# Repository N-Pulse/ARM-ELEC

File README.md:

# N-Pulse Prosthetic Safety System

> **EPFL N-Pulse — Spring Semester 2026**  
> Firmware and GUI for the safety monitoring board of the N-Pulse transradial bionic arm prosthesis.  
> For background on sensor selection rationale, thresholds, and design decisions, refer to the accompanying report.

---

## Repository Structure

```
/
├── GUI/
│   └── serial_dashboard.py        # Plotly Dash web dashboard — reads serial CSV and plots live telemetry
│
└── prosthetic_safety/
    ├── prosthetic_safety.ino      # Arduino sketch entry point (setup + loop)
    ├── Config.h                   # ⬅ All pin assignments, I2C addresses, thresholds — edit here first
    ├── DataTypes.h / .cpp         # Structs (TH_Reading, PowerReading, IMUReading, SafetyFlags) and global sensor objects
    ├── Setup.h / .cpp             # Sensor initialisation and interrupt attachment
    ├── Sensors.h / .cpp           # Sensor read functions (non-blocking DS18B20, SHT41, Si7021, INA260, LIS3DH)
    ├── Safety.h / .cpp            # Fault evaluation logic + ISR handlers
    ├── Logging.h / .cpp           # CSV serial output and SD card stub
    └── Utils.h / .cpp             # Helpers: ROM printing, threshold lookups, raw IMU register I/O
```

---

## Hardware Connections

The system uses two I2C buses on the Adafruit Metro ESP32-S3. Bus 0 (`Wire`, default pins) and Bus 1 (`Wire1`, pins 9 SDA / 10 SCL) are both active simultaneously.

### Pin Map (from `Config.h`)

| Signal | ESP32-S3 Pin | Connected to |
|--------|-------------|--------------|
| SDA0 | Pin SDA | DS2484 bus0, INA260, LIS3DH, SHT41 bus0 |
| SCL0 | Pin SCL | Same as above |
| SDA1 | Pin 9 | DS2484 bus1, SHT41 bus1, Si7021 |
| SCL1 | Pin 10 | Same as above |
| 1-Wire direct | Pin 7 | Battery, socket, and 1 motor DS18B20 (no bridge chip) |
| IMU interrupt | Pin 5 | LIS3DH INT1 → MCU (active-low, pull-up enabled) |
| Current alert | Pin 6 | INA260 ALERT → MCU (active-low, pull-up enabled, latching) |
| Power cut | Pin 11 | Pololu switch CTRL — pull **LOW** to cut load power |

### Wiring Diagram

#### JST cable labels

#### Current interupt test-bench wiring

Depending on the setup, it may be beneficial to make sure VIN- is the same as the systems GND (e.g. when using a lab alim), then wire like on the image (with the jumper). When trying to use the sensor on the test bench with the battery for example, simple pass the high or low cable of the battery through the VIN+ to VIN-. You might want remove the jumper and potentiometer to avoid any confusion in the wiring (unless the grounding is still useful). 

#### Full test-bench

Refer to this image to wire the test bench correctly.

Also note there are 3D printed motor mounts (orange), which can be used to test the motor under load and the thermal sensors. 

#### System-level block diagram and hand-level schematic: 

### I2C Address Map

| Device | Bus | Address | Notes |
|--------|-----|---------|-------|
| DS2484 (×2) | 0 and 1 | `0x18` | Fixed — one per bus to avoid collision |
| LIS3DH | 0 | `0x19` | SDO tied HIGH |
| INA260 | 0 | `0x40` | A0/A1 default |
| SHT41 (×2) | 0 and 1 | `0x44` | Fixed — one per bus to avoid collision |
| Si7021 | 1 | `0x40` | Shares bus 1 with SHT41, different from INA260 on bus 0 |

### DS18B20 Temperature Sensor Topology

Nine DS18B20s are distributed across three 1-Wire lines:

- **Bus 0 (via DS2484 on I2C bus 0):** 3 motor sensors in the hand
- **Bus 1 (via DS2484 on I2C bus 1):** 3 motor sensors in the hand
- **Direct line (pin 7, no bridge):** battery sensor, socket/stump contact sensor, 1 motor sensor

Each DS18B20 line needs a **4.7 kΩ pull-up resistor between DQ and 3.3 V** (but the ones passed in I2C already have a sufficient pullup resistance through the DS2484). The direct line uses the `DallasTemperature` library at **9-bit resolution** (94 ms conversion time, 0.5 °C) for faster updates. The DS2484-bridged lines use the `Adafruit_DS248x` library and the same 94 ms window.

### Power Cut Circuit

```
Battery (+) ──► Power Switch VIN ──► Prosthetic rail (+)
Battery (−) ──► Power Switch GND            ──► Prosthetic rail (−)
                        │
               ESP32-S3 Pin 11 ──► CTRL (LOW = power cut)
```

`PIN_POWER_CUT` is driven LOW by either the main loop (`requestPowerCut()`) or directly from the ISR for minimum latency on overcurrent and shock events.

---

## Sensor Discovery & Address Registration

**When new DS18B20 sensors are installed, their ROM addresses must be registered in `Config.h`.** (This should be already correct if the test-bench wasn't changed.) The firmware will print every discovered ROM to the serial monitor at startup — run the sketch once, note the ROM codes, then fill in the `bus0_sensors[]`, `bus1_sensors[]`, and `direct_sensors[]` arrays with the appropriate `SensorPurpose` and per-sensor temperature limit.

```cpp
// Example entry in Config.h
static constexpr SensorMapping direct_sensors[] = {
  {{ 0x28, 0xFF, 0x64, 0x0E, 0x6D, 0x54, 0x36, 0xC9 }, SensorPurpose::BATTERY, 45.0f },
  {{ 0x28, 0xFF, 0x64, 0x0E, 0x6D, 0x86, 0x2C, 0xE3 }, SensorPurpose::SOCKET,  41.0f },
  ...
};
```

Per-sensor limits (battery: 45 °C, socket contact: 41 °C, motors: 85 °C) are looked up at runtime by ROM address in `getSensorTempLimit()` (`Utils.cpp`). If a sensor's ROM is not in the table, it falls back to `MAX_TEMP_C`.

---

## INA260 Current Sensor — Bench Test

The INA260 sits in **series** with the battery. Before installing in the arm, validate it on a bench:

### Wiring for the test

```
Bench PSU (+) ──► INA260 IN+ ──► INA260 IN− ──► Load ──► Bench PSU (−)
                     │
              I2C to ESP32-S3 (bus 0, address 0x40)
              ALERT pin → ESP32-S3 pin 6
```

> ⚠️ The INA260 has **no galvanic isolation** between the battery ground and the board ground. Make sure both share the same ground reference, or use an isolated bench PSU. (That is the case on the test-bench)

### Recommended bench settings

| Parameter | Value |
|-----------|-------|
| PSU voltage | **12 V** |
| PSU current limit | **100 mA** |

The alert pin is configured in hardware for **overcurrent** (fires when current exceeds `Config::MAX_CURRENT_MA`). During bench testing, `MAX_CURRENT_MA` is set to 40 mA so the alert fires well within the PSU limit — set it back to 5300 mA (or appropriate value) for normal prosthetic operation.

---

## Arduino Libraries Required

Install all of the following via the Arduino Library Manager before compiling:

| Library | Used for |
|---------|---------|
| `Adafruit_INA260` | Current/voltage sensor |
| `Adafruit_LIS3DH` + `Adafruit_Sensor` | IMU |
| `Adafruit_Si7021` | Humidity/temp sensor (socket) |
| `7semi_SHT4x` | Humidity/temp sensors (hand/wrist) |
| `Adafruit_DS248x` | I2C-to-1-Wire bridge (DS2484) |
| `DallasTemperature` | Direct 1-Wire DS18B20 (no bridge) |
| `OneWire` | Required by DallasTemperature |

**Board:** Adafruit Metro ESP32-S3 (install via Arduino Boards Manager → search "esp32" by Espressif).

---

## Uploading the Firmware

1. Open `prosthetic_safety/prosthetic_safety.ino` in Arduino IDE.
2. Select **Board → Adafruit Metro ESP32-S3** and the correct COM/tty port.
3. Upload. On first boot, watch the serial monitor at **115 200 baud** — setup messages are prefixed with `[SETUP]`. Any sensor not found will print a warning; the ROM addresses of all discovered DS18B20s are printed here for registration.

---

## GUI — Live Telemetry Dashboard

`GUI/serial_dashboard.py` is a Plotly Dash web app. It reads the CSV stream from the serial port and displays five real-time subplots plus status LEDs for each safety flag.

### Install dependencies

```bash
pip install pyserial dash plotly pandas
```

### Configure the port

Edit the top of `serial_dashboard.py`:

```python
SERIAL_PORT   = '/dev/cu.usbmodem101'   
BAUD_RATE     = 115200
```
Replace with the correct port address. 

### Run

```bash
python GUI/serial_dashboard.py
```

Then open **http://127.0.0.1:8050** in any browser. The dashboard auto-reconnects if the serial connection drops.

### What is displayed

| Panel | Channels |
|-------|---------|
| Motor Temperatures | bus0_ds1–3, bus1_ds1–3, direct_ds1, socket contact, battery |
| Body Temperatures | Hand, wrist, socket ambient (SHT41 + Si7021) |
| Relative Humidity | Hand, wrist, socket (SHT41 + Si7021) |
| IMU Data | ax, ay, az [g] + vector magnitude |
| Power Data | Current [mA], voltage [V], power [mW] |
| Status LEDs | Temp limit, humidity limit, overcurrent, shock, power cut, sensors OK |

At startup the dashboard performs a one-time health check: any channel that reads `nan`, 0.0 (humidity), or below −10 °C (temperature) is automatically deselected. You can re-enable channels manually using the checklist below the plots.

### CSV format

The firmware emits one comma-separated line every 500 ms (configurable via `Config::LOG_PERIOD_MS`). Lines starting with `#` are ignored by the dashboard. The exact column order is:

```
t_ms, hand_temp_c, hand_rh, wrist_temp_c, wrist_rh, socket_temp_c, socket_rh,
bus0_ds1_c, bus0_ds2_c, bus0_ds3_c, bus1_ds1_c, bus1_ds2_c, bus1_ds3_c,
battery, socket, direct_ds1_c,
imu_ax_g, imu_ay_g, imu_az_g, imu_mag_g,
current_ma, bus_mv, power_mw,
temp_limit_flag, humidity_limit_flag, overcurrent_limit_flag,
shock_flag, power_cut_flag, sensors_ok
```

The code defaults with `PRINT_CSV_HEADER_AT_BOOT = false`. To have the CSV header printed at startup for easier CSV reading, simply set that to `true`.

---

## Enabling Power Cut Actions

All four power-cut triggers are **disabled by default** in `Config.h` for safe development:

```cpp
static const bool ENABLE_POWER_CUT_ON_OVERCURRENT        = false;
static const bool ENABLE_POWER_CUT_ON_OVERHEAT           = false;
static const bool ENABLE_POWER_CUT_ON_OVERHUMIDITY       = false;
static const bool ENABLE_POWER_CUT_ON_CONFIRMED_SHOCK    = false;
```

Set the relevant flag(s) to `true` once you have validated each sensor path end-to-end. The overcurrent and shock paths trigger from the ISR (minimum latency); overheat and humidity are evaluated in the main loop every `LOG_PERIOD_MS`.

Once a power cut is triggered, it **latches** — the flag does not reset automatically. A manual reset (power cycle or serial command) is required before the safety system will re-arm.

## Troubleshooting

If one of the lines is not being detected, it often happens that the pins are not well plugged in on the MCU (the pins tend to slip out).

## What to Add Next

- **SD card logging** — `logToSDCard()` in `Logging.cpp` is empty. The Metro ESP32-S3 has a built-in MicroSD slot and it would be a useful feature for the safety system. 
- **Using MCU Wireless capabilities** — The ESP32-S3 supports WiFi and Bluetooth; useful for reading data without cable connection with the arm.
- **CAN / UART protocol** — Define how fault codes are forwarded to the main prosthetic control board.
- **Prediction capabilities** - The MCU was chosen with a little extra horse power to be able to handle more demanding computations. One idea was to compute gradients and estiimate if one of the metrics was going to exceed the threshold and add a warning. 

## Other

There are two Adafruit DS2484 1Wire to I2C breakout boards left in the box with the test bench.

## Contributors

| Name | Role | Semester |
|------|------|----------|
| Mathis Finckh | Safety System Design & Implementation | Spring 2026 |

*Please update this table when you pick up the project.*

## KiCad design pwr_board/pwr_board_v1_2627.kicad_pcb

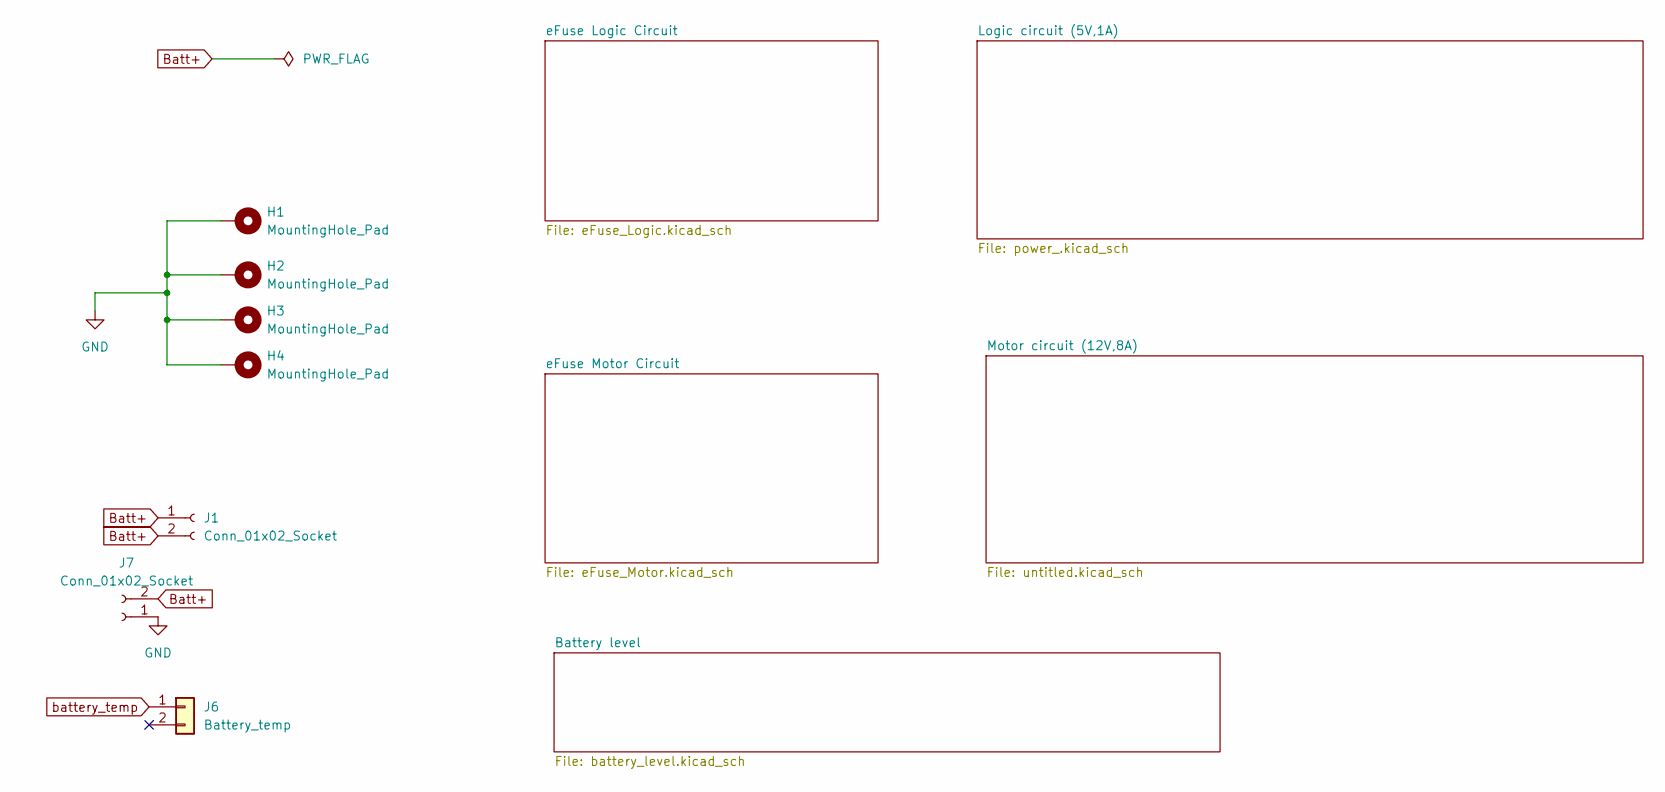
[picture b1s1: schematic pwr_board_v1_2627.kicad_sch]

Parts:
H1, H2, H3, H4: MountingHole_Pad; MountingHole_2.1mm
J1: Conn_01x02_Socket; SolderWire-0.75sqmm_1x02_P4.8mm_D1.25mm_OD2.3mm
J6: Battery_temp; Conn_12V_2A5040500291
J7: Conn_01x02_Socket; AMASS_XT30PW-F_1x02_P2.50mm_Horizontal

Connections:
Batt+: J1.1, J1.2, J7.2; also elsewhere on the board
GND: H1.1, H2.1, H3.1, H4.1, J7.1; also elsewhere on the board
battery_temp: J6.1 (Pin_1_1); also elsewhere on the board

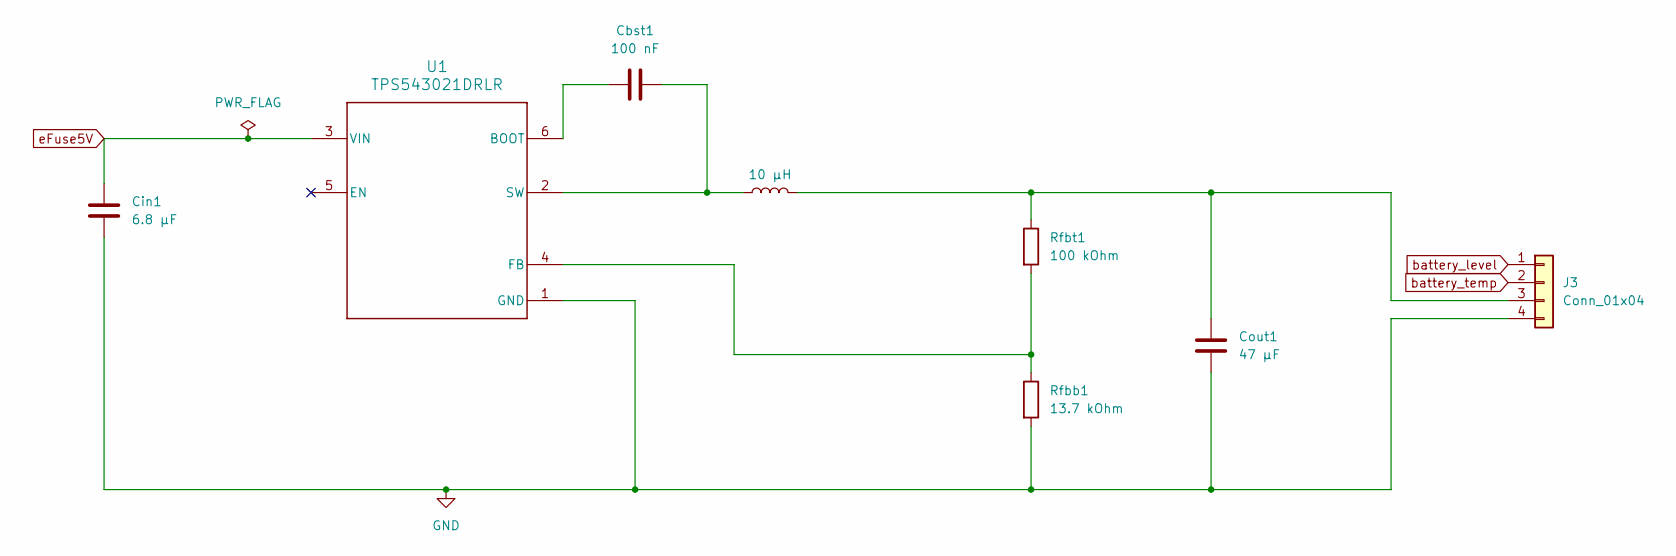
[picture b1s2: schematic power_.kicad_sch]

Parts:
Cbst1: 100 nF; C_0603_1608Metric
Cin1: 6.8 µF; C_0603_1608Metric
Cout1: 47 µF; C_0603_1608Metric
J3: Conn_01x04; 01x04_PicoLocck_Con_5037630491
L2: 10 µH; L2_74438324100
Rfbb1: 13.7 kOhm; R_0402_1005Metric
Rfbt1: 100 kOhm; R_0402_1005Metric
U1: TPS543021DRLR; Buck-5V-1A-TPS543021DRL

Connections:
GND: Cin1.2, Cout1.2, J3.4, Rfbb1.2, U1.1 (GND); also elsewhere on the board
unnamed: Cout1.1, J3.3, L2.2, Rfbt1.1
unnamed: Cbst1.1, U1.6 (BOOT)
unnamed: Rfbb1.1, Rfbt1.2, U1.4 (FB)
unnamed: Cbst1.2, L2.1, U1.2 (SW)
battery_level: J3.1; also elsewhere on the board
battery_temp: J3.2; also elsewhere on the board
eFuse5V: Cin1.1, U1.3 (VIN); also elsewhere on the board

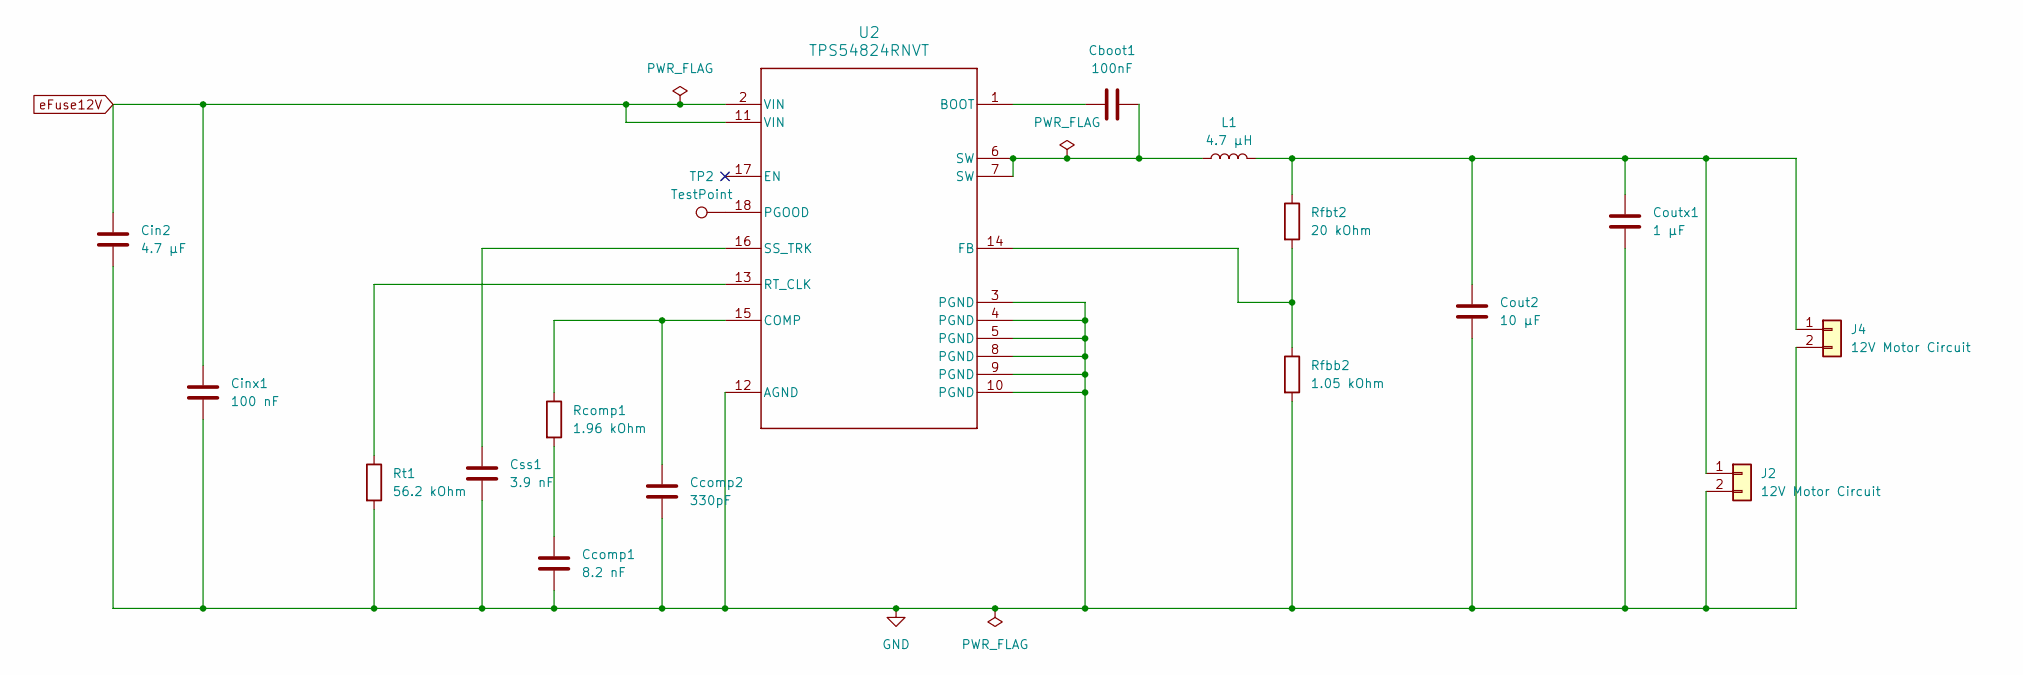
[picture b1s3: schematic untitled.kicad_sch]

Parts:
Cboot1: 100nF; C_0603_1608Metric
Ccomp1: 8.2 nF; C_0603_1608Metric
Ccomp2: 330pF; C_0603_1608Metric
Cin2: 4.7 µF; C_0603_1608Metric
Cinx1: 100 nF; C_0603_1608Metric
Cout2: 10 µF; C_0603_1608Metric
Coutx1: 1 µF; C_0603_1608Metric
Css1: 3.9 nF; C_0603_1608Metric
J2: 12V Motor Circuit; Conn_12V_2A5040500291
J4: 12V Motor Circuit; conn_12_6A__2053380000-SD_02_MOL
L1: 4.7 µH; L1_SRP5030HMCT100M
Rcomp1: 1.96 kOhm; R_0402_1005Metric
Rfbb2: 1.05 kOhm; R_0402_1005Metric
Rfbt2: 20 kOhm; R_0402_1005Metric
Rt1: 56.2 kOhm; R_0402_1005Metric
TP2: TestPoint; TestPoint_THTPad_1.5x1.5mm_Drill0.7mm
U2: TPS54824RNVT; MotorCircuit-Buck-12V-8A-TPS54824RNVT

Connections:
GND: Ccomp1.2, Ccomp2.2, Cin2.2, Cinx1.2, Cout2.2, Coutx1.2, Css1.2, J2.2, J4.2, Rfbb2.2, Rt1.2, U2.3 (PGND), U2.4 (PGND), U2.5 (PGND), U2.8 (PGND), U2.9 (PGND), U2.10 (PGND), U2.12 (AGND); also elsewhere on the board
unnamed: Cboot1.2, L1.1, U2.6 (SW), U2.7 (SW)
unnamed: Ccomp1.1, Rcomp1.2
unnamed: Cout2.1, Coutx1.1, J2.1, J4.1, L1.2, Rfbt2.1
unnamed: Cboot1.1, U2.1 (BOOT)
unnamed: Ccomp2.1, Rcomp1.1, U2.15 (COMP)
unnamed: Rfbb2.1, Rfbt2.2, U2.14 (FB)
unnamed: TP2.1 (1_1), U2.18 (PGOOD)
unnamed: Rt1.1, U2.13 (RT_CLK)
unnamed: Css1.1, U2.16 (SS_TRK)
eFuse12V: Cin2.1, Cinx1.1, U2.2 (VIN), U2.11 (VIN); also elsewhere on the board

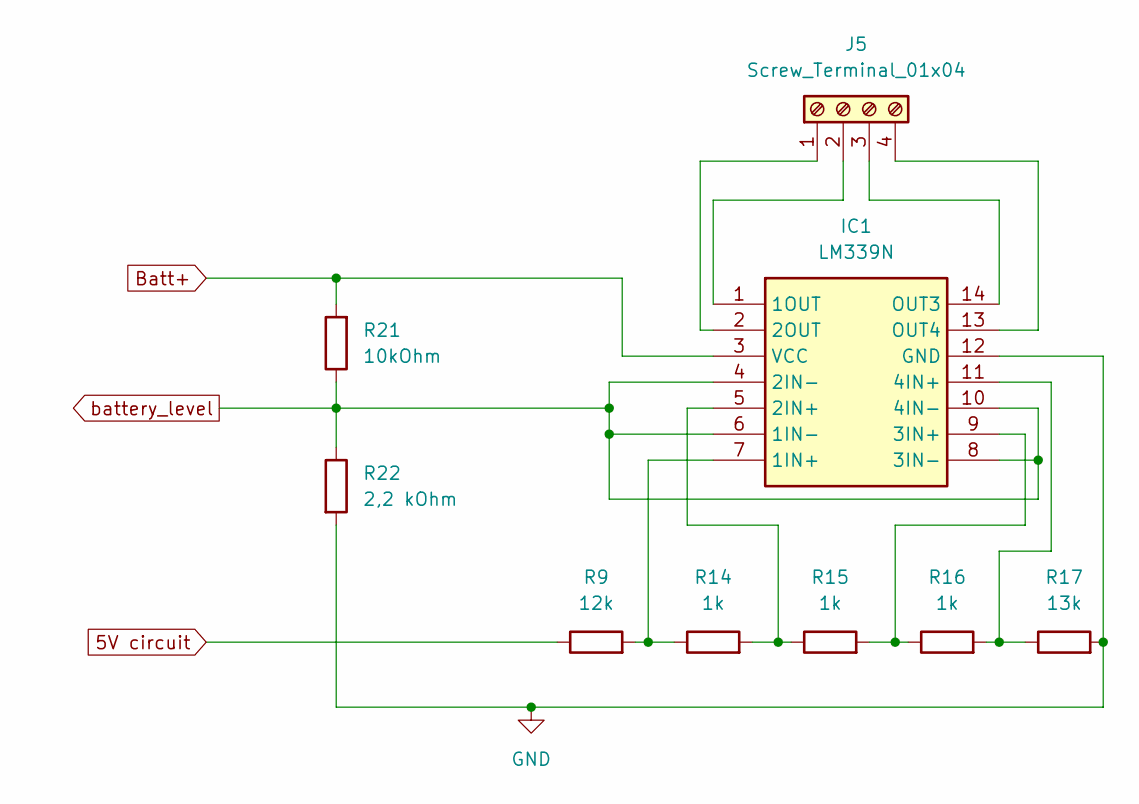
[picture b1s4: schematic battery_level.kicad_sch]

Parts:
IC1: LM339N; SOP65P640X120-14N_batt_lvl; Mouser Part Number 595-LM339N
J5: Screw_Terminal_01x04; 01x04_PicoLocck_Con_5037630491
R9: 12k; R_0402_1005Metric
R14, R15, R16: 1k; R_0402_1005Metric
R17: 13k; R_0402_1005Metric
R21: 10kOhm; R_0402_1005Metric
R22: 2,2 kOhm; R_0402_1005Metric

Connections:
5V circuit: R9.1
Batt+: IC1.3 (VCC), R21.2; also elsewhere on the board
GND: IC1.12 (GND), R17.2, R22.2; also elsewhere on the board
unnamed: IC1.7 (1IN+), R9.2, R14.1
unnamed: IC1.1 (1OUT), J5.2
unnamed: IC1.5 (2IN+), R14.2, R15.1
unnamed: IC1.2 (2OUT), J5.1
unnamed: IC1.9 (3IN+), R15.2, R16.1
unnamed: IC1.11 (4IN+), R16.2, R17.1
unnamed: IC1.14 (OUT3), J5.3
unnamed: IC1.13 (OUT4), J5.4
battery_level: IC1.4 (2IN-), IC1.6 (1IN-), IC1.8 (3IN-), IC1.10 (4IN-), R21.1, R22.1; also elsewhere on the board

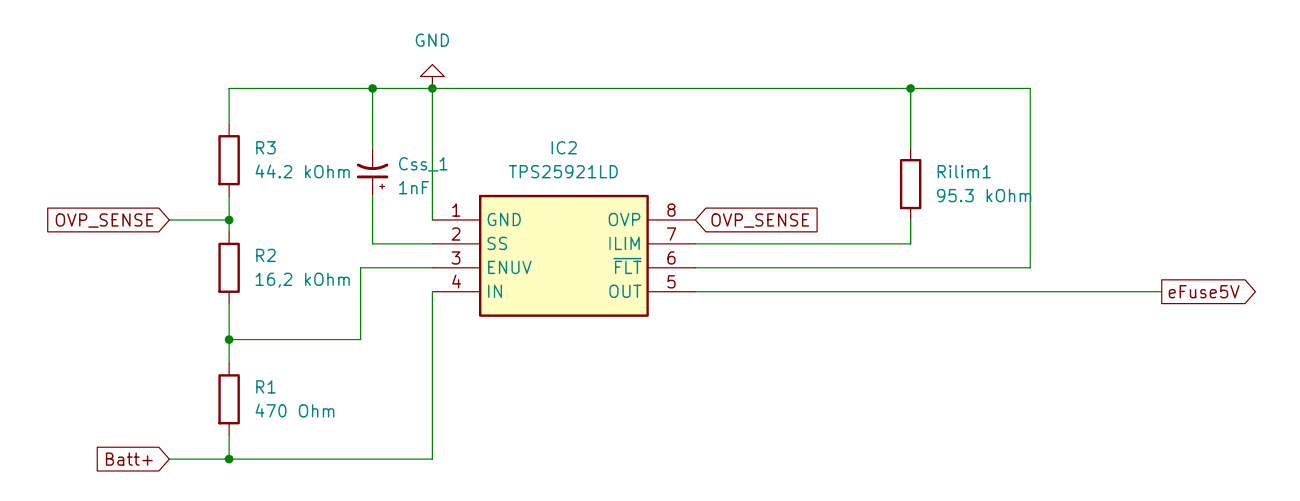
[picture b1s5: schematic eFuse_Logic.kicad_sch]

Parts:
Css_1: 1nF; C_0603_1608Metric
IC2: TPS25921LD; eFuse_Logic; Mouser Part Number 595-TPS25921LD
R1: 470 Ohm; R_0402_1005Metric
R2: 16,2 kOhm; R_0402_1005Metric
R3: 44.2 kOhm; R_0402_1005Metric
Rilim1: 95.3 kOhm; R_0402_1005Metric

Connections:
Batt+: IC2.4 (IN), R1.2; also elsewhere on the board
GND: Css_1.2, IC2.1 (GND), IC2.6 (~FLT), R3.1, Rilim1.1; also elsewhere on the board
unnamed: IC2.3 (ENUV), R1.1, R2.2
unnamed: IC2.7 (ILIM), Rilim1.2
unnamed: Css_1.1, IC2.2 (SS)
OVP_SENSE: IC2.8 (OVP), R2.1, R3.2
eFuse5V: IC2.5 (OUT); also elsewhere on the board

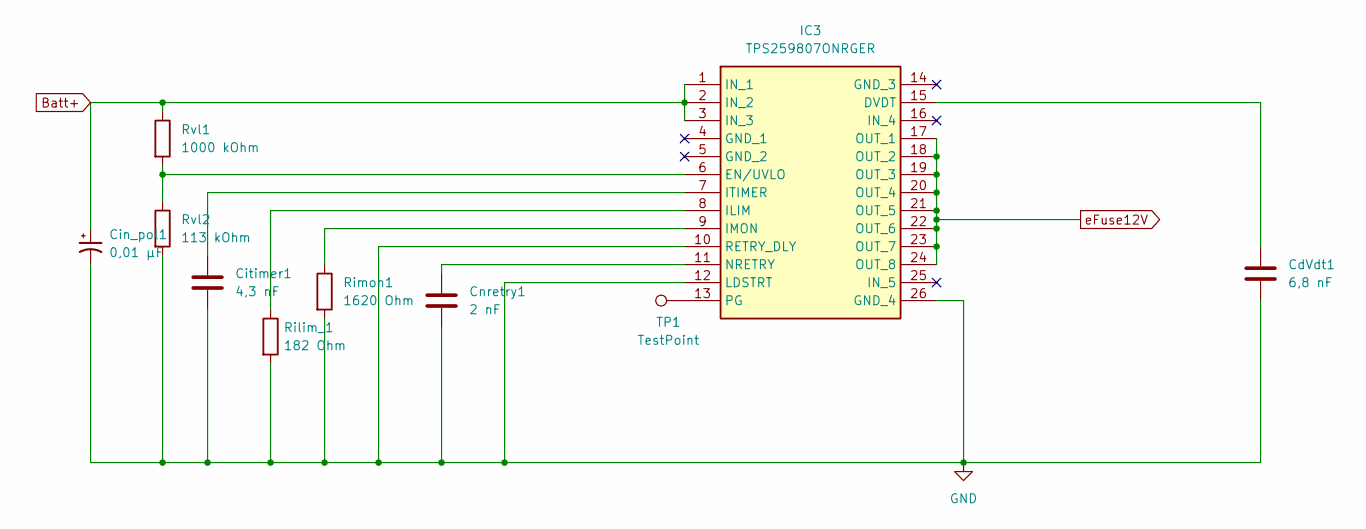
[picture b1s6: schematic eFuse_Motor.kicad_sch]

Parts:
CdVdt1: 6,8 nF; C_0603_1608Metric
Cin_pol1: 0,01 µF; C_0603_1608Metric
Citimer1: 4,3 nF; C_0603_1608Metric
Cnretry1: 2 nF; C_0603_1608Metric
IC3: TPS259807ONRGER; eFuse_Motor; Mouser Part Number 595-TPS259807ONRGER
Rilim_1: 182 Ohm; R_0402_1005Metric
Rimon1: 1620 Ohm; R_0402_1005Metric
Rvl1: 1000 kOhm; R_0402_1005Metric
Rvl2: 113 kOhm; R_0402_1005Metric
TP1: TestPoint; TestPoint_THTPad_1.5x1.5mm_Drill0.7mm

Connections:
Batt+: Cin_pol1.1, IC3.1 (IN_1), IC3.2 (IN_2), IC3.3 (IN_3), Rvl1.1; also elsewhere on the board
GND: CdVdt1.2, Cin_pol1.2, Citimer1.2, Cnretry1.2, IC3.10 (RETRY_DLY), IC3.12 (LDSTRT), IC3.26 (GND_4), Rilim_1.2, Rimon1.2, Rvl2.2; also elsewhere on the board
unnamed: CdVdt1.1, IC3.15 (DVDT)
unnamed: IC3.6 (EN/UVLO), Rvl1.2, Rvl2.1
unnamed: IC3.8 (ILIM), Rilim_1.1
unnamed: IC3.9 (IMON), Rimon1.1
unnamed: Citimer1.1, IC3.7 (ITIMER)
unnamed: Cnretry1.1, IC3.11 (NRETRY)
unnamed: IC3.13 (PG), TP1.1 (1_1)
eFuse12V: IC3.17 (OUT_1), IC3.18 (OUT_2), IC3.19 (OUT_3), IC3.20 (OUT_4), IC3.21 (OUT_5), IC3.22 (OUT_6), IC3.23 (OUT_7), IC3.24 (OUT_8); also elsewhere on the board

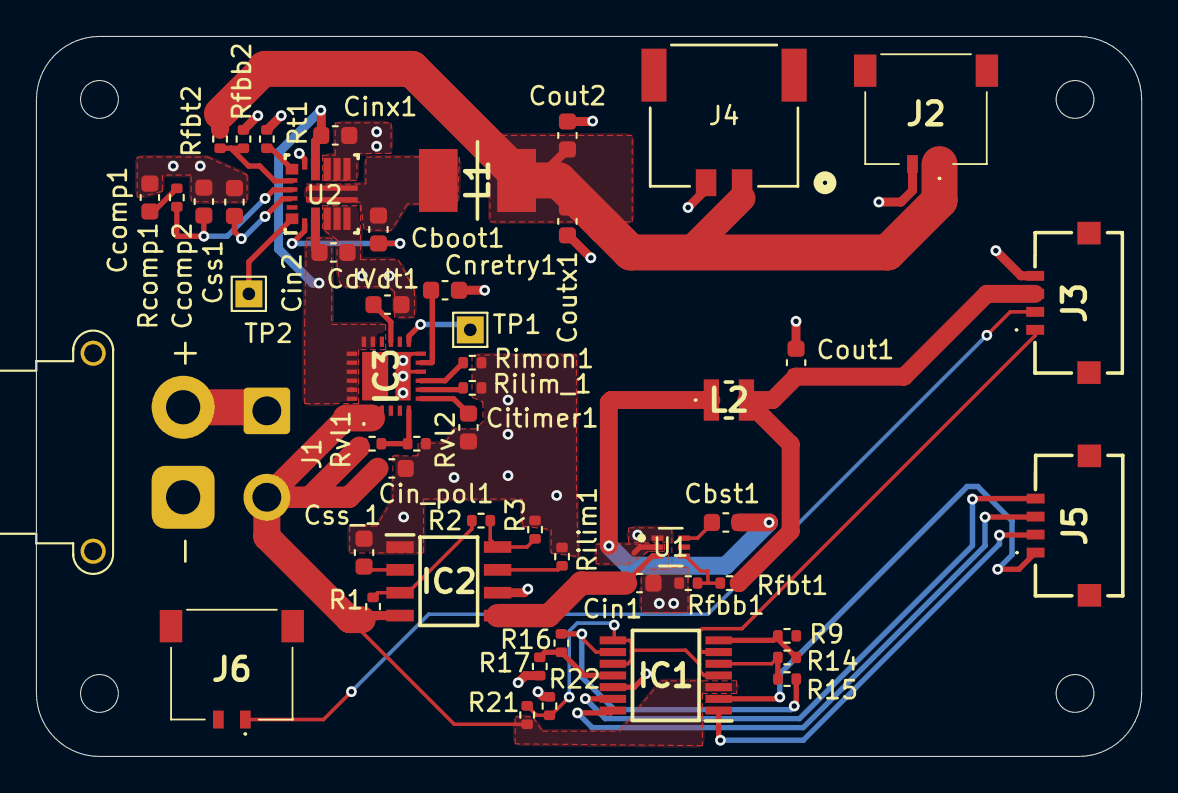
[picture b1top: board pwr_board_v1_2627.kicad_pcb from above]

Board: 2 copper layers, 61.4 x 40.0 mm, 57 parts (0 on the bottom side), 38 nets.

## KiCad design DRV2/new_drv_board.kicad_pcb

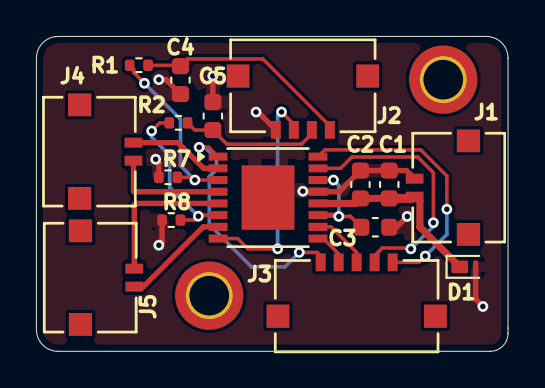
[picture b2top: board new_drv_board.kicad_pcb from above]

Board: 2 copper layers, 26.2 x 17.5 mm, 18 parts (0 on the bottom side), 17 nets.

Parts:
C1: 0.1µF; C_0603_1608Metric
C2: 10µF; C_0603_1608Metric
C3: 2.2µF; C_0603_1608Metric
C4, C5: 100nF; C_0603_1608Metric
D1: PTVS12VZ1USK; Nexperia_DSN1608-2_1.6x0.8mm
H1, H2: MountingHole; MountingHole_2.2mm_M2_DIN965_Pad_TopBottom
J1, J5: Conn_01x02; CONN_5037630000-SD_02_MOL
J2: Conn_01x04; CONN_5037630000-SD_04_MOL
J3: Conn_01x05; CONN_5037630000-SD_05_MOL
J4: CONN_5037630000-SD_02_MOL
R1, R2: 100Ω; R_0402_1005Metric
R7, R8: 500mΩ; R_0402_1005Metric
U1: DRV8848; TSSOP-16-1EP_4.4x5mm_P0.65mm

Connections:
+12V: C1.1, C2.1, D1.1 (K), J1.1, U1.12 (VM)
/Curr7: R1.1, R7.1, U1.3 (AISEN)
/Curr8: R2.1, R8.1, U1.6 (BISEN)
/IN7-1: J3.5, U1.16 (AIN1)
/IN7-2: J3.4, U1.15 (AIN2)
/IN8-1: J3.2, U1.9 (BIN1)
/IN8-2: J3.3, U1.10 (BIN2)
/OUT7-1: J4.1, U1.2 (AOUT1)
/OUT7-2: J4.2, U1.4 (AOUT2)
/OUT8-1: J5.2, U1.7 (BOUT1)
/OUT8-2: J5.1, U1.5 (BOUT2)
/nFAULT: J2.3, U1.8 (~FAULT)
/sleep: J3.1, U1.1 (~SLEEP)
GND: C1.2, C2.2, C3.2, C4.1, C5.2, D1.2 (A), J1.2, J2.4, R7.2, R8.2, U1.13 (GND), U1.17 (GND)
unnamed: C4.2, J2.1, R1.2
unnamed: C5.1, J2.2, R2.2
unnamed: C3.1, U1.11 (VREF), U1.14 (VINT)

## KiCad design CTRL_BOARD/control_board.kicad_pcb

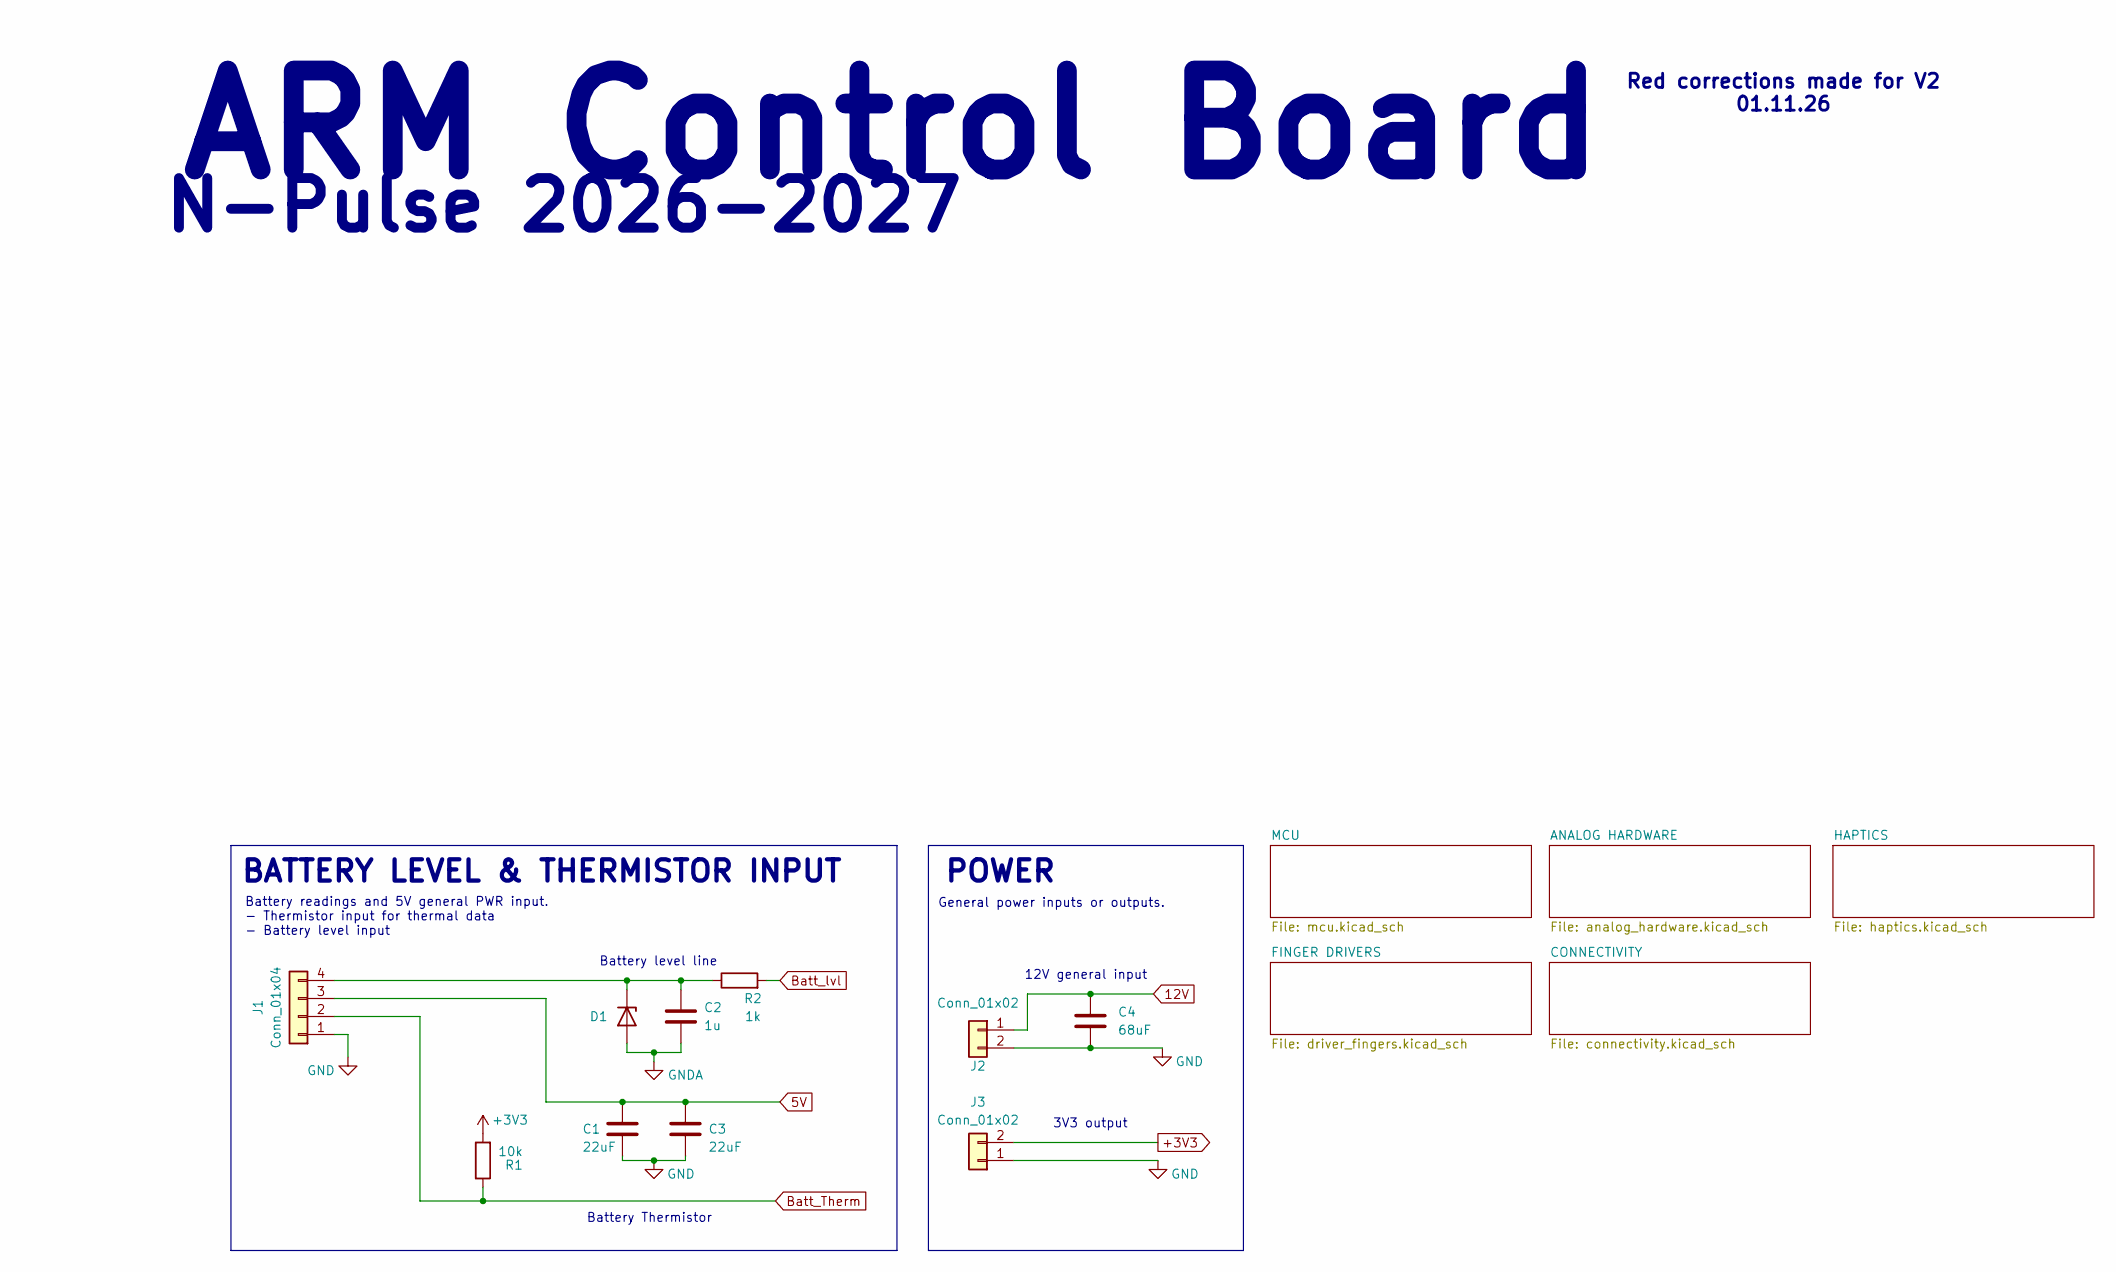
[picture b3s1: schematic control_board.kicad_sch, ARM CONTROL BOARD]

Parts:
C1, C3: 22uF; C_0805_2012Metric
C2: 1u; C_0402_1005Metric
C4: 68uF; CAP_EEEFK1C680AP
D1: PESD5V0L1UL; D_SOD-882
J1: Conn_01x04; CONN_5037630000-SD_04_MOL
J2: Conn_01x02; CONN_2053380000-SD_02_MOL
J3: Conn_01x02; CONN_5037630000-SD_02_MOL
R1: 10k; R_0402_1005Metric
R2: 1k; R_0402_1005Metric

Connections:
5V: C1.1, C3.1, J1.3; also elsewhere on the board
12V: C4.1, J2.1; also elsewhere on the board
+3V3: J3.2, R1.2; also elsewhere on the board
Batt_Therm: J1.2, R1.1
Batt_lvl: R2.2; also elsewhere on the board
GND: C1.2, C2.2, C3.2, C4.2, D1.2 (A), J1.1, J2.2, J3.1; also elsewhere on the board
unnamed: C2.1, D1.1 (K), J1.4, R2.1

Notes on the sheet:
3V3 output
Battery readings and 5V general PWR input. - Thermistor input for thermal data - Battery level input
ARM Control Board
POWER
BATTERY LEVEL & THERMISTOR INPUT
Red corrections made for V2 01.11.26
Battery level line
N-Pulse 2026-2027
12V general input
Battery Thermistor
General power inputs or outputs.
